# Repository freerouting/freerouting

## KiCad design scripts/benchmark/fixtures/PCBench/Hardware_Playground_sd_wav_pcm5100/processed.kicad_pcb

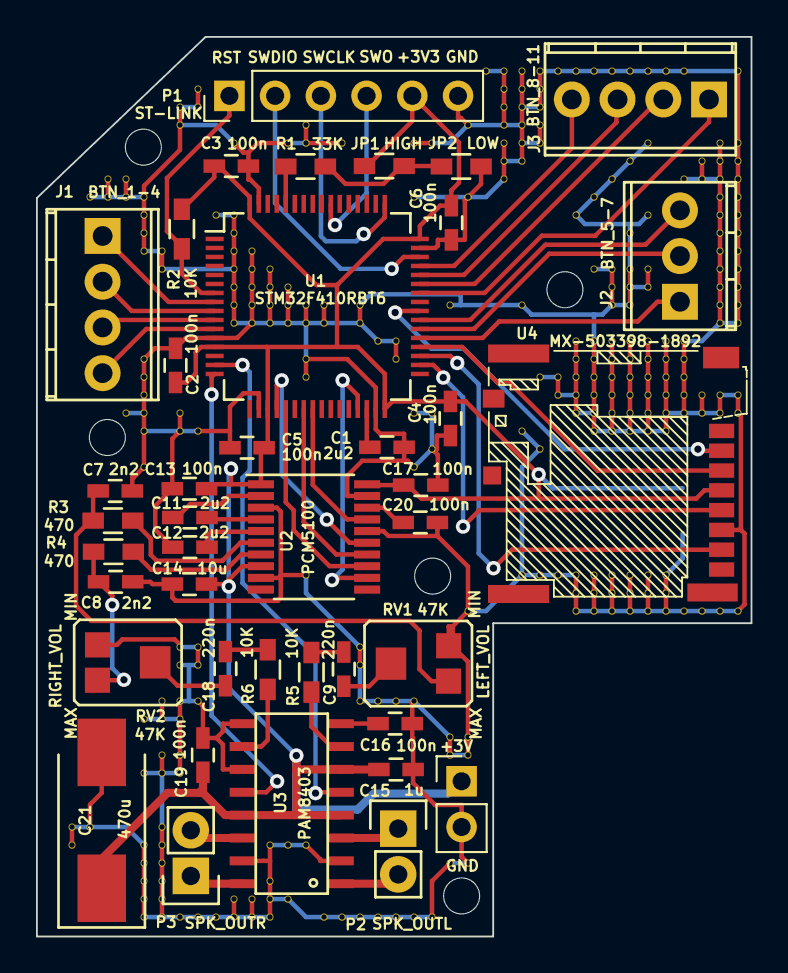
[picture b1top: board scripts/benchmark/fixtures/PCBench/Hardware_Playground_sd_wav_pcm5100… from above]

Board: 2 copper layers, 39.7 x 50.0 mm, 323 parts (1 on the bottom side), 50 nets.

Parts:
C1, C11, C14: 2u2; C_0603_HandSoldering
C2, C3, C4, C5, C6, C13, C16, C17, C19, C20: 100n; C_0603_HandSoldering
C7, C8: 2n2; C_0603_HandSoldering
C9, C18: 220n; C_0603_HandSoldering
C10: 47u; C_0805_HandSoldering
C12: 10u; C_0603_HandSoldering
C15: 1u; C_0603_HandSoldering
C21: 470u; Tantalum_Case-D_EIA-7343-31_Hand
J1: BTN_1-4; TerminalBlock_Pheonix_MPT-2.54mm_4pol
J2: BTN_5-7; TerminalBlock_Pheonix_MPT-2.54mm_3pol
J3: BTN_8-11; TerminalBlock_Pheonix_MPT-2.54mm_4pol
JP1: HIGH; R_0603_HandSoldering
JP2: LOW; R_0603_HandSoldering
P1: ST-LINK; Pin_Header_Straight_1x06_Pitch2.54mm
P2: SPK_OUTL; Pin_Header_Straight_1x02
P3: SPK_OUTR; Pin_Header_Straight_1x02
P4: Supply; Pin_Header_Straight_1x02_Pitch2.54mm
R1: 33K; R_0603_HandSoldering
R2, R5, R6: 10K; R_0603_HandSoldering
R3, R4: 470; R_0603_HandSoldering
RV1, RV2: 47K; TC-33X-2
U1: STM32F410RBT6; LQFP-64_10x10mm_Pitch0.5mm
U2: PCM5100; TSSOP-20_4.4x6.5mm_Pitch0.65mm
U3: PAM8403; SOP16L
U4: MX-503398-1892
V2_44, V2_45, V3_9, V3_44, V4_8, V4_9, V5_8, V5_9, V5_21, V6_9, V6_10, V6_11, V6_12, V6_18, V6_19, V6_20, V6_21, V6_22, V6_24, V6_38, V6_41, V6_45, V6_46, V6_47, V6_48, V6_49, V7_12, V7_13, V7_37, V7_38, V7_40, V7_41, V7_44, V7_45, V7_46, V7_47, V7_48, V7_49, V8_4, V8_5, V8_21, V8_22, V8_34, V8_35, V8_37, V8_38, V8_40, V8_41, V8_49, V9_3, V9_4, V9_22, V9_34, V9_35, V9_37, V9_49, V10_10, V10_49, V11_6, V11_10, V11_11, V11_12, V11_13, V11_14, V11_15, V11_16, V11_48, V11_49, V12_12, V12_13, V12_14, V12_15, V12_16, V12_48, V12_49, V13_13, V13_14, V13_15, V13_16, V13_45, V13_47, V13_48, V13_49, V14_6, V14_14, V14_15, V14_16, V14_45, V14_48, V15_5, V15_6, V15_15, V15_16, V15_18, V15_19, V15_30, V15_45, V16_15, V16_16, V16_49, V17_6, V17_49, V18_15, V18_16, V18_34, V18_35, V18_37, V18_49, V19_17, V19_37, V19_49, V20_17, V20_18, V20_37, V20_49, V21_6, V21_9, V21_21, V21_24, V21_37, V21_49, V22_6, V22_21, V22_23, V22_49, V23_15, V23_39, V23_40, V23_46, V24_5, V24_9, V24_32, V24_39, V24_40, V24_46, V25_2, V26_2, V26_3, V26_4, V26_5, V26_6, V26_7, V26_8, V27_2, V27_3, V27_4, V27_5, V27_6, V27_7, V27_15, V27_22, V27_30, V28_2, V28_3, V28_4, V28_5, V28_6, V28_19, V28_23, V28_30, V29_2, V29_19, V29_20, V29_30, V30_2, V30_10, V30_17, V30_18, V30_19, V30_20, V30_21, V30_30, V30_31, V30_32, V31_2, V31_9, V31_13, V31_17, V31_18, V31_19, V31_20, V31_21, V31_22, V31_30, V31_31, V31_32, V32_2, V32_8, V32_13, V32_14, V32_15, V32_17, V32_18, V32_19, V32_20, V32_21, V32_22, V32_30, V32_31, V32_32, V33_2, V33_7, V33_11, V33_13, V33_14, V33_15, V33_17, V33_18, V33_19, V33_20, V33_21, V33_22, V33_30, V33_31, V33_32, V34_2, V34_6, V34_10, V34_13, V34_14, V34_17, V34_18, V34_19, V34_20, V34_21, V34_22, V34_30, V34_31, V34_32, V35_2, V35_17, V35_18, V35_19, V35_20, V35_21, V35_22, V35_30, V35_31, V35_32, V36_2, V36_8, V36_17, V36_18, V36_19, V36_20, V36_21, V36_32, V37_7, V37_8, V37_20, V37_21, V37_32, V38_6, V38_7, V38_8, V38_9, V38_10, V38_11, V38_12, V38_13, V38_14, V38_15, V38_16, V38_20, V38_21, V38_32, V39_2, V39_6, V39_7, V39_8, V39_9, V39_10, V39_11, V39_12, V39_13, V39_14, V39_15, V39_16, V39_20, V39_21, V39_32: AUTO_VIA; VIA_MATRIX

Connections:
+3V3: C2.1, C3.1, C4.1, C5.1, C6.1, C10.1, C12.2, C13.1, C15.2, C17.1, C19.1, C21.1, JP1.2, P1.5, P4.1, R2.2, U1.13, U1.19, U1.32, U1.48, U1.64, U2.1, U2.8, U2.20, U3.4, U3.6, U3.13, U4.4
/BTN1: J1.1, U1.8
/BTN2: J1.2, U1.9
/BTN3: J1.3, U1.10
/BTN4: J1.4, U1.11
/BTN5: J2.1, U1.37
/BTN6: J2.2, U1.38
/BTN7: J2.3, U1.39
/BTN8: J3.1, U1.42
/BTN9: J3.2, U1.43
/BTN10: J3.3, U1.44
/BTN11: J3.4, U1.45
/I2S_BCLK: U1.21, U2.13
/I2S_DATA: U1.23, U2.14
/I2S_LRCLK: U1.20, U2.15
/I2S_MCLK: U1.29, U2.12
/PAM8403_MUTE: U1.15, U3.5
/PAM8403_STANDBY: U1.16, U3.12
/PCM5100_MUTE: U1.24, U2.17
/PCM5100_OUTL: C7.2, R3.2, RV1.1
/PCM5100_OUTR: C8.2, R4.2, RV2.3
/SD_CS: U1.40, U4.2
/SD_DI: U1.36, U4.3
/SD_DO: U1.35, U4.7
/SD_SCLK: U1.34, U4.5
/SWCLK: P1.3, U1.49
/SWDIO: P1.2, U1.46
/SWO: P1.4, U1.55
/nRST: P1.1, R2.1, U1.7
GND: C1.2, C2.2, C3.2, C4.2, C5.2, C6.2, C7.1, C8.1, C10.2, C12.1, C13.2, C14.2, C15.1, C16.1, C17.2, C19.2, C20.2, C21.2, JP2.1, P1.6, P4.2, RV1.3, RV2.1, U1.12, U1.18, U1.31, U1.47, U1.63, U2.3, U2.9, U2.16, U2.19, U3.2, U3.9, U3.11, U3.15, U4.6, V2_44.1, V2_45.1, V3_9.1, V3_44.1, V4_8.1, V4_9.1, V5_8.1, V5_9.1, V5_21.1, V6_9.1, V6_10.1, V6_11.1, V6_12.1, V6_18.1, V6_19.1, V6_20.1, V6_21.1, V6_22.1, V6_24.1, V6_38.1, V6_41.1, V6_45.1, V6_46.1, V6_47.1, V6_48.1, V6_49.1, V7_12.1, V7_13.1, V7_37.1, V7_38.1, V7_40.1, V7_41.1, V7_44.1, V7_45.1, V7_46.1, V7_47.1, V7_48.1, V7_49.1, V8_4.1, V8_5.1, V8_21.1, V8_22.1, V8_34.1, V8_35.1, V8_37.1, V8_38.1, V8_40.1, V8_41.1, V8_49.1, V9_3.1, V9_4.1, V9_22.1, V9_34.1, V9_35.1, V9_37.1, V9_49.1, V10_10.1, V10_49.1, V11_6.1, V11_10.1, V11_11.1, V11_12.1, V11_13.1, V11_14.1, V11_15.1, V11_16.1, V11_48.1, V11_49.1, V12_12.1, V12_13.1, V12_14.1, V12_15.1, V12_16.1, V12_48.1, V12_49.1, V13_13.1, V13_14.1, V13_15.1, V13_16.1, V13_45.1, V13_47.1, V13_48.1, V13_49.1, V14_6.1, V14_14.1, V14_15.1, V14_16.1, V14_45.1, V14_48.1, V15_5.1, V15_6.1, V15_15.1, V15_16.1, V15_18.1, V15_19.1, V15_30.1, V15_45.1, V16_15.1, V16_16.1, V16_49.1, V17_6.1, V17_49.1, V18_15.1, V18_16.1, V18_34.1, V18_35.1, V18_37.1, V18_49.1, V19_17.1, V19_37.1, V19_49.1, V20_17.1, V20_18.1, V20_37.1, V20_49.1, V21_6.1, V21_9.1, V21_21.1, V21_24.1, V21_37.1, V21_49.1, V22_6.1, V22_21.1, V22_23.1, V22_49.1, V23_15.1, V23_39.1, V23_40.1, V23_46.1, V24_5.1, V24_9.1, V24_32.1, V24_39.1, V24_40.1, V24_46.1, V25_2.1, V26_2.1, V26_3.1, V26_4.1, V26_5.1, V26_6.1, V26_7.1, V26_8.1, V27_2.1, V27_3.1, V27_4.1, V27_5.1, V27_6.1, V27_7.1, V27_15.1, V27_22.1, V27_30.1, V28_2.1, V28_3.1, V28_4.1, V28_5.1, V28_6.1, V28_19.1, V28_23.1, V28_30.1, V29_2.1, V29_19.1, V29_20.1, V29_30.1, V30_2.1, V30_10.1, V30_17.1, V30_18.1, V30_19.1, V30_20.1, V30_21.1, V30_30.1, V30_31.1, V30_32.1, V31_2.1, V31_9.1, V31_13.1, V31_17.1, V31_18.1, V31_19.1, V31_20.1, V31_21.1, V31_22.1, V31_30.1, V31_31.1, V31_32.1, V32_2.1, V32_8.1, V32_13.1, V32_14.1, V32_15.1, V32_17.1, V32_18.1, V32_19.1, V32_20.1, V32_21.1, V32_22.1, V32_30.1, V32_31.1, V32_32.1, V33_2.1, V33_7.1, V33_11.1, V33_13.1, V33_14.1, V33_15.1, V33_17.1, V33_18.1, V33_19.1, V33_20.1, V33_21.1, V33_22.1, V33_30.1, V33_31.1, V33_32.1, V34_2.1, V34_6.1, V34_10.1, V34_13.1, V34_14.1, V34_17.1, V34_18.1, V34_19.1, V34_20.1, V34_21.1, V34_22.1, V34_30.1, V34_31.1, V34_32.1, V35_2.1, V35_17.1, V35_18.1, V35_19.1, V35_20.1, V35_21.1, V35_22.1, V35_30.1, V35_31.1, V35_32.1, V36_2.1, V36_8.1, V36_17.1, V36_18.1, V36_19.1, V36_20.1, V36_21.1, V36_32.1, V37_7.1, V37_8.1, V37_20.1, V37_21.1, V37_32.1, V38_6.1, V38_7.1, V38_8.1, V38_9.1, V38_10.1, V38_11.1, V38_12.1, V38_13.1, V38_14.1, V38_15.1, V38_16.1, V38_20.1, V38_21.1, V38_32.1, V39_2.1, V39_6.1, V39_7.1, V39_8.1, V39_9.1, V39_10.1, V39_11.1, V39_12.1, V39_13.1, V39_14.1, V39_15.1, V39_16.1, V39_20.1, V39_21.1, V39_32.1
unnamed: C1.1, U1.30
unnamed: C9.1, R5.2
unnamed: C9.2, RV1.2
unnamed: C11.1, U2.4
unnamed: C11.2, U2.2
unnamed: C14.1, U2.5
unnamed: C16.2, U3.8
unnamed: C18.1, RV2.2
unnamed: C18.2, R6.1
unnamed: C20.1, U2.18
unnamed: JP1.1, JP2.2, R1.2
unnamed: P2.1, U3.3
unnamed: P2.2, U3.1
unnamed: P3.1, U3.16
unnamed: P3.2, U3.14
unnamed: R1.1, U1.60
unnamed: R3.1, U2.6
unnamed: R4.1, U2.7
unnamed: R5.1, U3.7
unnamed: R6.2, U3.10

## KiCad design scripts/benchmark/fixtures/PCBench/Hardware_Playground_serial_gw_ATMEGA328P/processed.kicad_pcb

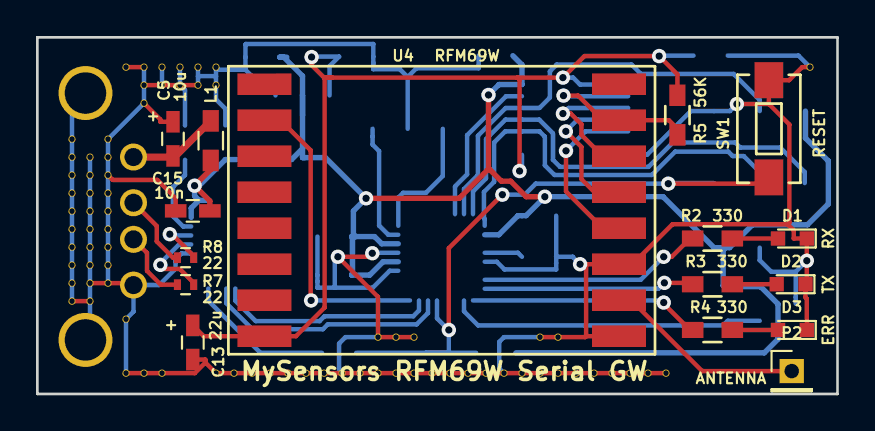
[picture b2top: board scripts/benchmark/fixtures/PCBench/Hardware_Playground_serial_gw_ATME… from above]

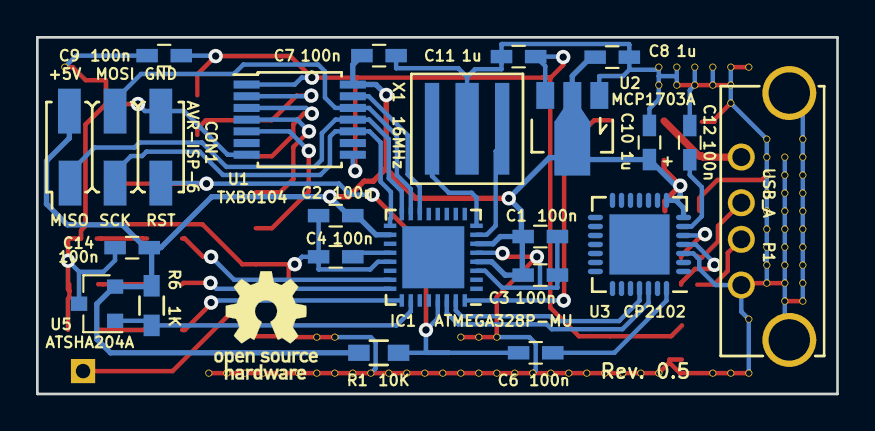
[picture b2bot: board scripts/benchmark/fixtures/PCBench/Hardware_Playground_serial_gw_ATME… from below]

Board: 2 copper layers, 44.5 x 19.8 mm, 114 parts (21 on the bottom side), 33 nets.

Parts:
C1, C2, C3, C4, C6, C7, C9, C12, C14: 100n; C_0603_HandSoldering
C5: 10u; C_0603_HandSoldering
C8, C10, C11: 1u; C_0603_HandSoldering
C13: 22u; C_0603_HandSoldering
C15: 10n; C_0603_HandSoldering
CON1: AVR-ISP-6; AVR_ISP_SMT_Small_02x03
D1: RX; LED_0603
D2: TX; LED_0603
D3: ERR; LED_0603
IC1: ATMEGA328P-MU; QFN-32-1EP_5x5mm_Pitch0.5mm
L1: BLM18HE152SN1D; R_0603_HandSoldering
P1: USB_A; USB_A_bottom
P2: ANTENNA; Pin_Header_Straight_1x01_Pitch2.00mm
R1: 10K; R_0603_HandSoldering
R2, R3, R4: 330; R_0603_HandSoldering
R5: 56K; R_0603_HandSoldering
R6: 1K; R_0603_HandSoldering
R7, R8: 22; R_0402
SW1: RESET; SW_SPST_EVQPE1
U1: TXB0104; TSSOP-14_4.4x5mm_Pitch0.65mm
U2: MCP1703A; SOT89-3_Housing
U3: CP2102; QFN-28-1EP_5x5mm_Pitch0.5mm
U4: RFM69W; RFM69HW_SMD_Handsoldering
U5: ATSHA204A; SOT-23
V2_7, V2_8, V2_9, V2_10, V2_11, V2_12, V2_13, V2_14, V2_15, V2_16, V3_8, V3_9, V3_10, V3_11, V3_12, V3_13, V3_14, V3_15, V3_16, V4_7, V4_8, V4_9, V4_10, V4_11, V4_12, V4_13, V4_14, V4_15, V5_3, V5_17, V5_20, V6_3, V6_4, V6_5, V6_20, V7_3, V7_4, V7_20, V8_3, V8_4, V9_3, V9_4, V10_3, V10_4, V10_20, V11_20, V12_20, V13_20, V14_20, V15_20, V16_20, V17_20, V18_20, V19_18, V19_20, V20_18, V20_20, V21_18, V21_20, V22_20, V23_20, V24_20, V25_20, V26_20, V27_20, V28_18, V28_20, V29_18, V29_20, V30_20, V31_20, V32_20, V33_20, V34_20, V35_20, V43_3: AUTO_VIA; VIA_MATRIX
X1: 16MHz; ZTTCS-3

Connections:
+3V3: C9.2, C11.1, C13.1, R5.2, U1.1, U1.8, U2.3, U4.8
+5V: C1.1, C2.2, C3.2, C7.1, C8.1, C10.2, C14.1, C15.2, CON1.2, IC1.4, IC1.6, IC1.18, L1.1, R1.1, R6.2, U1.14, U2.2, U3.7, U3.8, U5.2
/ATSHA204A: IC1.26, R6.1, U5.1
/DTR: C6.2, U3.28
/GW_ERR_LED: IC1.25, R4.2
/GW_RX_LED: IC1.23, R2.2
/GW_TX_LED: IC1.24, R3.2
/MISO: CON1.1, IC1.16, U1.11
/MOSI: CON1.4, IC1.15, U1.12
/RFM69W_INT: IC1.32, U4.2
/RFM69W_SS: IC1.14, U1.13
/RST: C6.1, CON1.5, IC1.29, R1.2, SW1.1
/SCK: CON1.3, IC1.17, U1.10
/SER_RX: IC1.31, U3.25
/SER_TX: IC1.30, U3.26
GND: C1.2, C2.1, C3.1, C4.1, C5.1, C7.2, C8.2, C9.1, C10.1, C11.2, C12.2, C13.2, C14.2, C15.1, CON1.6, D1.1, D2.1, D3.1, IC1.3, IC1.5, IC1.21, P1.4, P1.5, SW1.2, U1.7, U2.1, U3.3, U4.9, U4.11, U5.3, V2_7.1, V2_8.1, V2_9.1, V2_10.1, V2_11.1, V2_12.1, V2_13.1, V2_14.1, V2_15.1, V2_16.1, V3_8.1, V3_9.1, V3_10.1, V3_11.1, V3_12.1, V3_13.1, V3_14.1, V3_15.1, V3_16.1, V4_7.1, V4_8.1, V4_9.1, V4_10.1, V4_11.1, V4_12.1, V4_13.1, V4_14.1, V4_15.1, V5_3.1, V5_17.1, V5_20.1, V6_3.1, V6_4.1, V6_5.1, V6_20.1, V7_3.1, V7_4.1, V7_20.1, V8_3.1, V8_4.1, V9_3.1, V9_4.1, V10_3.1, V10_4.1, V10_20.1, V11_20.1, V12_20.1, V13_20.1, V14_20.1, V15_20.1, V16_20.1, V17_20.1, V18_20.1, V19_18.1, V19_20.1, V20_18.1, V20_20.1, V21_18.1, V21_20.1, V22_20.1, V23_20.1, V24_20.1, V25_20.1, V26_20.1, V27_20.1, V28_18.1, V28_20.1, V29_18.1, V29_20.1, V30_20.1, V31_20.1, V32_20.1, V33_20.1, V34_20.1, V35_20.1, V43_3.1, X1.2
unnamed: C4.2, IC1.20
unnamed: C5.2, L1.2, P1.1
unnamed: C12.1, U3.6
unnamed: D1.2, R2.1
unnamed: D2.2, R3.1
unnamed: D3.2, R4.1
unnamed: IC1.7, X1.3
unnamed: IC1.8, X1.1
unnamed: P1.2, R8.2
unnamed: P1.3, R7.2
unnamed: P2.1, U4.10
unnamed: R5.1, U1.2, U4.15
unnamed: R7.1, U3.4
unnamed: R8.1, U3.5
unnamed: U1.3, U4.14
unnamed: U1.4, U4.13
unnamed: U1.5, U4.12

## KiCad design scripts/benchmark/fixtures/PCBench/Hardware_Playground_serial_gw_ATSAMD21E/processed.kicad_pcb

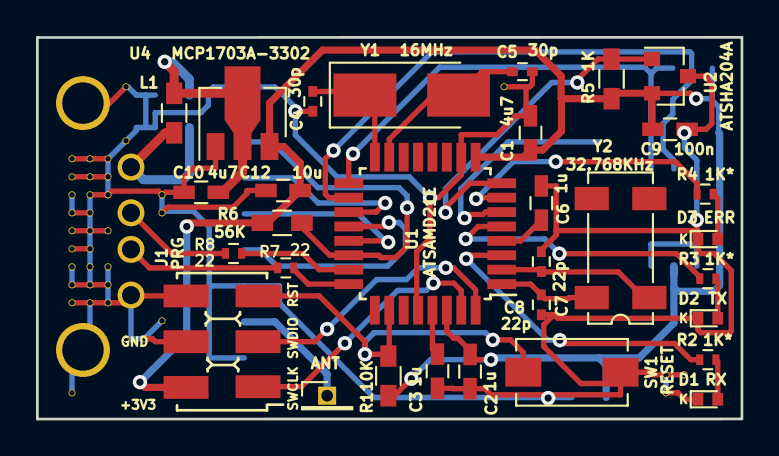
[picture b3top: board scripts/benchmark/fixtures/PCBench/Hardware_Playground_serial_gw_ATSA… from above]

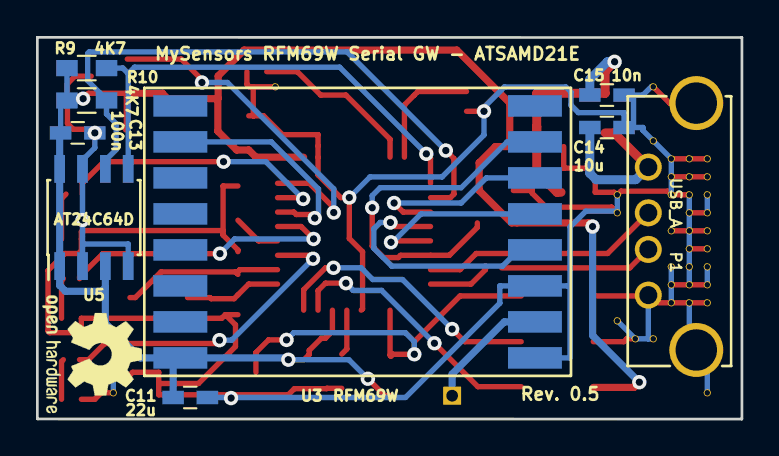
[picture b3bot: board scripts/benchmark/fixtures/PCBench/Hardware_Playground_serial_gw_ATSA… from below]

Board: 2 copper layers, 39.1 x 21.2 mm, 77 parts (8 on the bottom side), 32 nets.

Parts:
C1, C10: 4u7; C_0603_HandSoldering
C2, C3, C6: 1u; C_0603_HandSoldering
C4, C5: 30p; C_0402
C7, C8: 22p; C_0402
C9, C13: 100n; C_0603_HandSoldering
C11: 22u; C_0603_HandSoldering
C12, C14: 10u; C_0603_HandSoldering
C15: 10n; C_0603_HandSoldering
D1: RX; LED_0402
D2: TX; LED_0402
D3: ERR; LED_0402
J1: PRG; AVR_ISP_SMT_Small_02x03
L1: BLM18HE152SN1D; R_0603_HandSoldering
P1: USB_A; USB_A_bottom
P2: ANT; Pin_Header_Straight_1x01_Pitch1.27mm
R1: 10K; R_0603_HandSoldering
R2, R3, R4: 1K*; R_0402
R5: 1K; R_0603_HandSoldering
R6: 56K; R_0603_HandSoldering
R7, R8: 22; R_0402
R9, R10: 4K7; R_0603_HandSoldering
SW1: RESET; SW_SPST_EVQPE1
U1: ATSAMD21E; TQFP-32_7x7mm_Pitch0.8mm
U2: ATSHA204A; SOT-23
U3: RFM69W; RFM69HW_SMD_Handsoldering
U4: MCP1703A-3302; SOT89-3_Housing
U5: AT24C64D; SOIC-8_3.9x4.9mm_Pitch1.27mm
V2_7, V2_8, V2_9, V2_10, V2_11, V2_12, V2_13, V2_14, V2_15, V2_20, V3_7, V3_8, V3_9, V3_10, V3_11, V3_12, V3_13, V3_14, V3_15, V4_7, V4_8, V4_9, V4_11, V4_13, V4_14, V4_15, V5_3, V5_6, V5_17, V6_17, V7_9, V7_10, V7_16, V26_3, V35_19, V35_20, V36_19: AUTO_VIA; VIA_MATRIX
Y1: 16MHz; Crystal_SMD_5032-2pin_5.0x3.2mm_HandSoldering
Y2: 32.768KHz; Crystal_SMD_SeikoEpson_MC306-4pin_8.0x3.2mm

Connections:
+3V3: C1.1, C2.2, C9.1, C11.1, C12.1, C13.1, J1.2, R1.2, R5.2, R6.2, R9.2, R10.2, U1.9, U1.30, U2.2, U3.8, U4.3, U5.1, U5.3, U5.8
/ATSHA204A: R5.1, U1.8, U2.1
/GW_ERR_LED: R4.2, U1.7
/GW_RX_LED: R2.2, U1.3
/GW_TX_LED: R3.2, U1.5
/MISO: U1.21, U3.13
/MOSI: U1.19, U3.14
/RFM69W_INT: U1.6, U3.2
/RFM69W_SS: R6.1, U1.22, U3.15
/RST: J1.5, R1.1, SW1.1, U1.26
/SCK: U1.20, U3.12
/SCL: R10.1, U1.18, U5.6
/SDA: R9.1, U1.17, U5.5
/SWCLK: J1.1, U1.31
/SWDIO: J1.3, U1.32
/USBDM: R8.1, U1.23
/USBDP: R7.1, U1.24
/VBUS: C10.1, C15.2, L1.2, U4.2
GND: C1.2, C2.1, C3.2, C4.2, C5.2, C6.2, C7.2, C8.2, C9.2, C10.2, C11.2, C12.2, C13.2, C14.1, C15.1, D1.1, D2.1, D3.1, J1.4, J1.6, P1.4, P1.5, SW1.2, U1.10, U1.28, U2.3, U3.9, U3.11, U4.1, U5.2, U5.4, U5.7, V2_7.1, V2_8.1, V2_9.1, V2_10.1, V2_11.1, V2_12.1, V2_13.1, V2_14.1, V2_15.1, V2_20.1, V3_7.1, V3_8.1, V3_9.1, V3_10.1, V3_11.1, V3_12.1, V3_13.1, V3_14.1, V3_15.1, V4_7.1, V4_8.1, V4_9.1, V4_11.1, V4_13.1, V4_14.1, V4_15.1, V5_3.1, V5_6.1, V5_17.1, V6_17.1, V7_9.1, V7_10.1, V7_16.1, V26_3.1, V35_19.1, V35_20.1, V36_19.1
unnamed: C3.1, U1.29
unnamed: C4.1, U1.16, Y1.1
unnamed: C5.1, U1.15, Y1.2
unnamed: C6.1, U1.4
unnamed: C7.1, U1.2, Y2.1
unnamed: C8.1, U1.1, Y2.4
unnamed: C14.2, L1.1, P1.1
unnamed: D1.2, R2.1
unnamed: D2.2, R3.1
unnamed: D3.2, R4.1
unnamed: P1.2, R8.2
unnamed: P1.3, R7.2
unnamed: P2.1, U3.10
